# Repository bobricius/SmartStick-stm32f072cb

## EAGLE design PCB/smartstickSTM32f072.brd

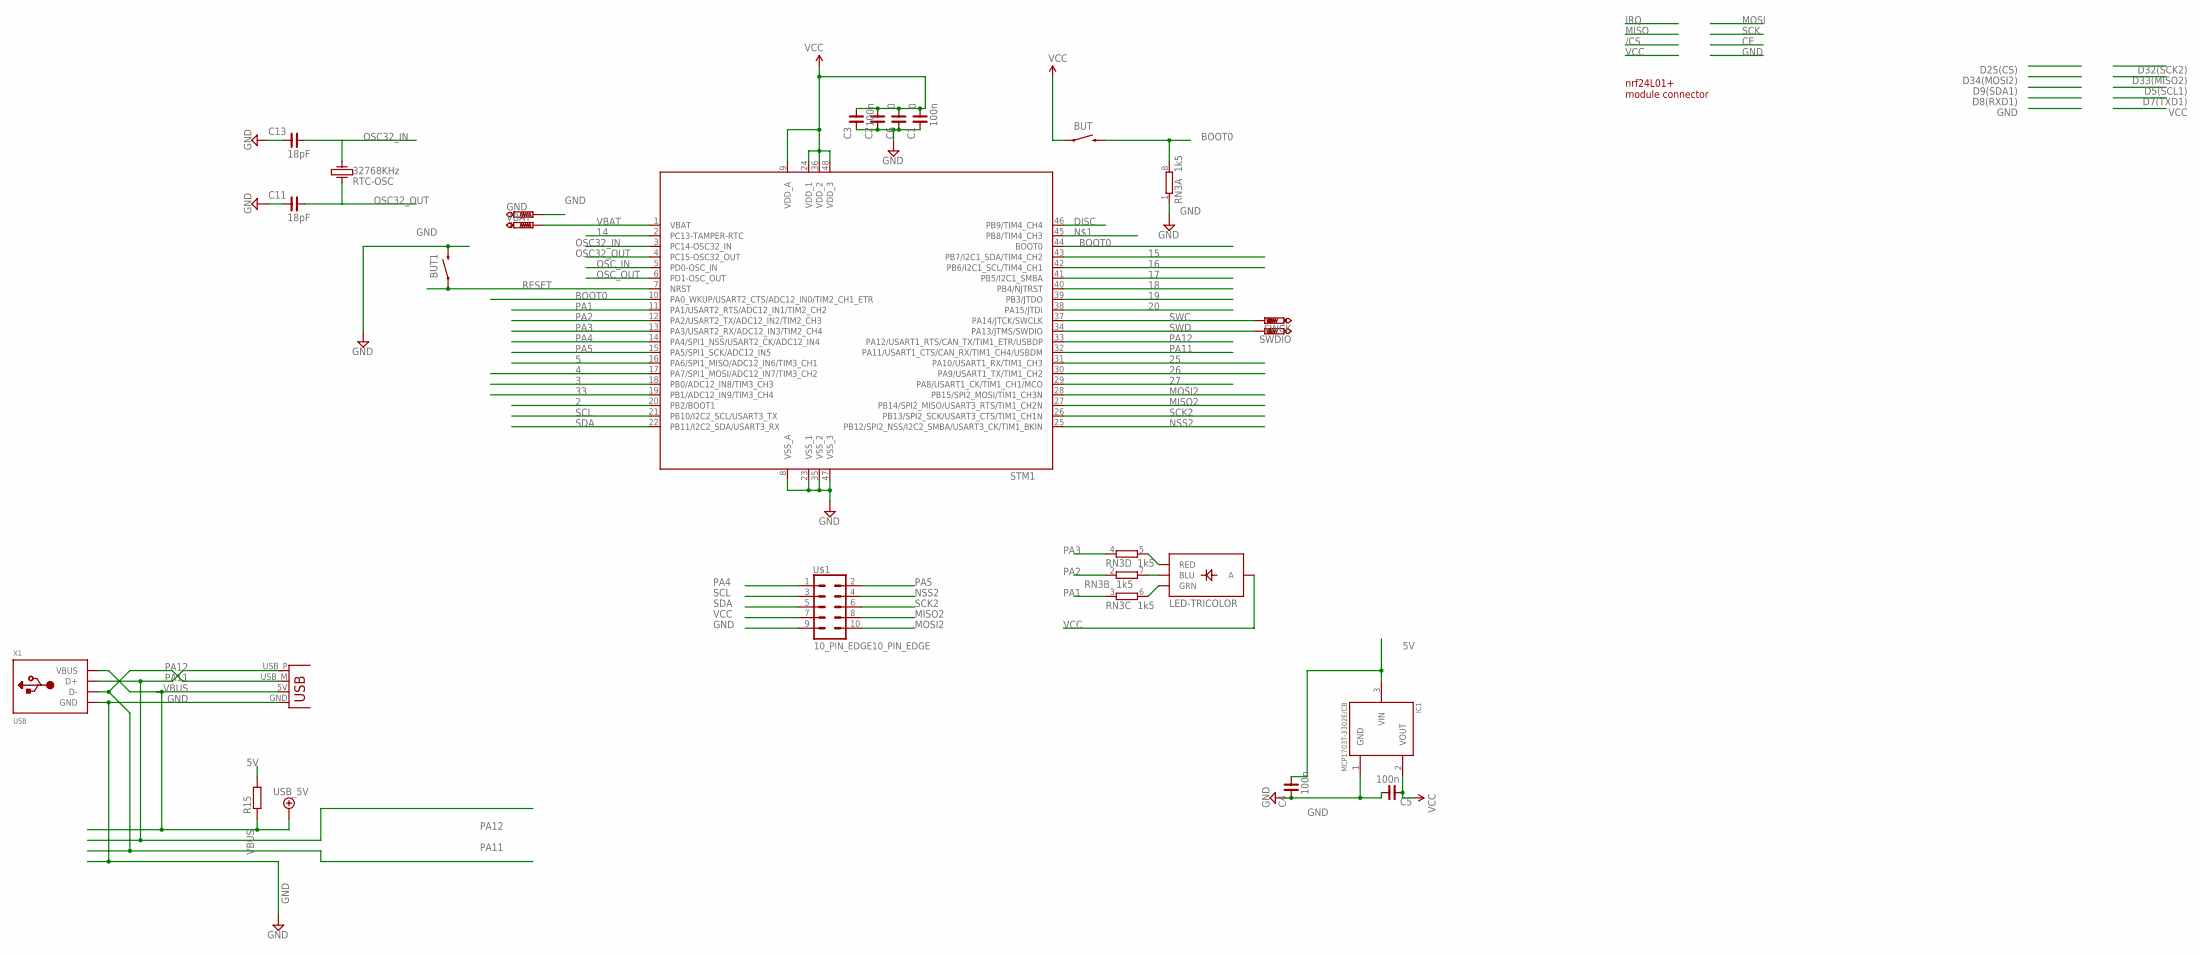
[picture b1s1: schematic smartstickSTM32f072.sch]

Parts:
BUT, BUT1: SWITCH-MOMENTARY-2-SMD-1101NE; TACTILE-SWITCH-1101NE
C1, C3, C4, C5: 100n; C0603
C2, C6: 0; C0603
C11, C13: 18pF; C0603
GND: PTR1TP20SQ; TP20SQ
IC1: MCP1703T-3302E/CB; SOT23
R15: R-EU_R0603; R0603
RN3: 1k5; EXB38V
RTC-OSC: 32768KHz; KX-327LT
STM1: STM32F103CB; LQFP48
SWCK: PTR1TP16R; TP16R
SWDIO: PTR1TP16R; TP16R
U$1: 10_PIN_EDGE10_PIN_EDGE; 10_PIN_EDGE
U$3: LED-TRICOLOR; LED-TRICOLOR-SMD
VBAT: PTR1TP19R; TP19R
X1: USB; MOLEX-48037-1000
X3: USBPCB; USB-A-PCB

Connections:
2: STM1.20 (PB2/BOOT1)
3: STM1.18 (PB0/ADC12_IN8/TIM3_CH3)
4: STM1.17 (PA7/SPI1_MOSI/ADC12_IN7/TIM3_CH2)
5: STM1.16 (PA6/SPI1_MISO/ADC12_IN6/TIM3_CH1)
5V: C4.1, IC1.3 (VIN), R15.2
14: STM1.2 (PC13-TAMPER-RTC)
15: STM1.43 (PB7/I2C1_SDA/TIM4_CH2)
16: STM1.42 (PB6/I2C1_SCL/TIM4_CH1)
17: STM1.41 (PB5/I2C1_SMBA)
18: STM1.40 (PB4/NJTRST)
19: STM1.39 (PB3/JTDO)
20: STM1.38 (PA15/JTDI)
25: STM1.31 (PA10/USART1_RX/TIM1_CH3)
26: STM1.30 (PA9/USART1_TX/TIM1_CH2)
27: STM1.29 (PA8/USART1_CK/TIM1_CH1/MCO)
33: STM1.19 (PB1/ADC12_IN9/TIM3_CH4)
BOOT0: BUT.P$2 (2), RN3.8 (2), STM1.10 (PA0_WKUP/USART2_CTS/ADC12_IN0/TIM2_CH1_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), STM1.44 (BOOT0)
DISC: STM1.46 (PB9/TIM4_CH4)
GND: BUT1.P$2 (2), C1.2, C2.2, C3.2, C4.2, C5.1, C6.2, C11.2, C13.2, GND.TP, IC1.1 (GND), RN3.1, STM1.8 (VSS_A), STM1.23 (VSS_1), STM1.35 (VSS_2), STM1.47 (VSS_3), U$1.9, X1.4 (GND), X3.GND
MISO2: STM1.27 (PB14/SPI2_MISO/USART3_RTS/TIM1_CH2N), U$1.8
MOSI2: STM1.28 (PB15/SPI2_MOSI/TIM1_CH3N), U$1.10
unnamed: RN3.5 (2), U$3.R (RED)
unnamed: RN3.7 (2), U$3.B (BLU)
unnamed: RN3.6 (2), U$3.G (GRN)
NSS2: STM1.25 (PB12/SPI2_NSS/I2C2_SMBA/USART3_CK/TIM1_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), U$1.4
OSC32_IN: C13.1, RTC-OSC.1, STM1.3 (PC14-OSC32_IN)
OSC32_OUT: C11.1, RTC-OSC.4, STM1.4 (PC15-OSC32_OUT)
OSC_IN: STM1.5 (PD0-OSC_IN)
OSC_OUT: STM1.6 (PD1-OSC_OUT)
PA1: RN3.3 (1), STM1.11 (PA1/USART2_RTS/ADC12_IN1/TIM2_CH2)
PA2: RN3.2 (1), STM1.12 (PA2/USART2_TX/ADC12_IN2/TIM2_CH3)
PA3: RN3.4 (1), STM1.13 (PA3/USART2_RX/ADC12_IN3/TIM2_CH4)
PA4: STM1.14 (PA4/SPI1_NSS/USART2_CK/ADC12_IN4), U$1.1
PA5: STM1.15 (PA5/SPI1_SCK/ADC12_IN5), U$1.2
PA11: STM1.32 (PA11/USART1_CTS/CAN_RX/TIM1_CH4/USBDM), X1.2 (D-), X3.USB_M (D-)
PA12: STM1.33 (PA12/USART1_RTS/CAN_TX/TIM1_ETR/USBDP), X1.3 (D+), X3.USB_P (D+)
RESET: BUT1.P$1 (1), STM1.7 (NRST)
SCK2: STM1.26 (PB13/SPI2_SCK/USART3_CTS/TIM1_CH1N), U$1.6
SCL: STM1.21 (PB10/I2C2_SCL/USART3_TX), U$1.3
SDA: STM1.22 (PB11/I2C2_SDA/USART3_RX), U$1.5
SWC: STM1.37 (PA14/JTCK/SWCLK), SWCK.TP
SWD: STM1.34 (PA13/JTMS/SWDIO), SWDIO.TP
VBAT: STM1.1 (VBAT), VBAT.TP
VBUS: R15.1, X1.1 (VBUS), X3.5V (VBUS)
VCC: BUT.P$1 (1), C1.1, C2.1, C3.1, C5.2, C6.1, IC1.2 (VOUT), STM1.9 (VDD_A), STM1.24 (VDD_1), STM1.36 (VDD_2), STM1.48 (VDD_3), U$1.7, U$3.A

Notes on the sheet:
BOOT0
nrf24L01+ module connector

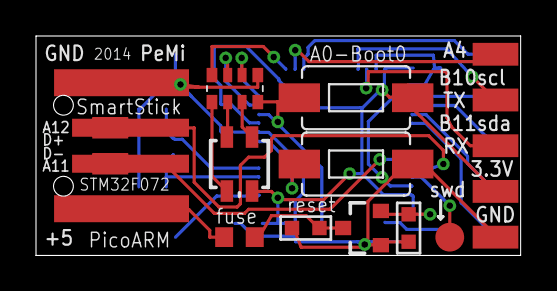
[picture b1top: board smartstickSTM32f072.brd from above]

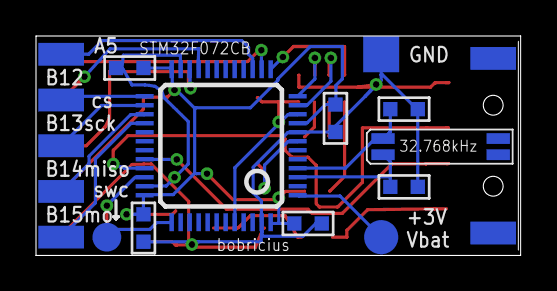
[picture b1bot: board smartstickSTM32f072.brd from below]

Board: 2 copper layers, 26.9 x 12.2 mm, 23 parts (11 on the bottom side), 27 nets.

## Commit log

2014-11-12 :neckbeard: Added .gitattributes & .gitignore files
2014-11-12 first upload

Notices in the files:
parts and their libraries:
SparkFun-LED: Licensing: CC v3.0 Share-Alike You are welcome to use this library for commercial purposes.
